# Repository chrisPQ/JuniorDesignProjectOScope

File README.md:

# JuniorDesignProjectOScope
Teensy program to run oscilloscope and output to screen

Video Overview: https://www.youtube.com/watch?v=Kpc6_z2Lm2U&ab_channel=MarshallG

Showcase Page: https://eecs.engineering.oregonstate.edu/project-showcase/projects/?id=eiNZnlOKVvULkvkf

Design Problem:
The design problem was to create a 2-channel oscilloscope. The scope needed to have voltage
scaling, time scaling, and trigger capabilities. The system also needs to have AC/DC coupling
modes, and a responsive interface.

Design process: The first step in our design process was to do some preliminary research to
see what it was we would need to accomplish the requirements. This included taking into
account the different choices of hardware we could use. We initially considered this project
based on a field programmable gate array due to the high sampling requirement that were
initially on the project instructions. After that requirement was removed, we went with our
second option, which was a Teensy 4.0 microcontroller board. We went with this option because
it is relatively inexpensive (especially compared to an FPGA), but it is still very fast with a clock
speed of 600 megahertz.

Our next big hurdle was figuring out how to implement the input circuitry. Since we decided our
input signal range was 0-20 volts peak to peak, and our microcontroller could only handle a
range of 0-3.3 volts, we had to adjust the signal to be able to measure it. We worked together on
designing the circuit and simulating the results in LTspice. We then soldered it to a protoboard
and experimented with the circuit in the lab. Our team had to work together to troubleshoot the
circuit and adjust the component values to perform as expected.

Although our whole system was split into individual blocks, we had to work together very closely
to ensure our systems would work as expected. For example, the input conditioning block has to
take voltage from the power supply block. Then the signal conversion and processing block had
to take input from the signal conditioning block.Communication about these individual tasks
made our system integration go smoother as the different pieces meshed together well.

Once all the circuit prototypes were designed and tested, we put them onto a PCB. We worked
together to peer review the PCB to ensure it would work correctly. Once the board arrived, we
used tools in the lab such as the oven and soldering irons to assemble the components onto the
board. This phase was a challenge as we included some very small surface mount parts in our
design. One challenge we had at this stage was that we had some slight mistakes in the PCB.
The pin header where the microcontroller was supposed to be ended up being one pin too
short. We fixed this by making an adapter board that mapped the pins of the MCU (expected
one two that we didn’t need) to a set of pin headers that was the correct number for the footprint
on the PCB.

We finished the process by working on our embedded software to control the device. This was a
challenge because it included meshing together code covering many different tasks, all of which
had challenges of their own.

Timeline:
April 19th: Engineering requirments devised.
April 26th: First block documentation.
May 1st: First Block verification.
May 10th: Second Block documentation
May 15th: Second block verification.
May 31st: System Verification.
June 5th: Demo of final project.

Takeaways:
Over the course of this project we learned about working on a complex project with a tight
deadline. This taught us many lessons of project management and how to focus on prioritizing
the important parts when it comes to developing electronics projects. Specifically we learned the
importance of researching and simulation methods before diving into them. While this may
seem restraining at first, it is a method that saves time and money in the long run because
things are more likely to work the first time around. We also learned many things about specific
technologies. Using direct memory access and interrupts to enhance the performance speed of
our microcontroller were concepts that required us to research and access data that wasn’t as
accessible as things we had worked on in the past.

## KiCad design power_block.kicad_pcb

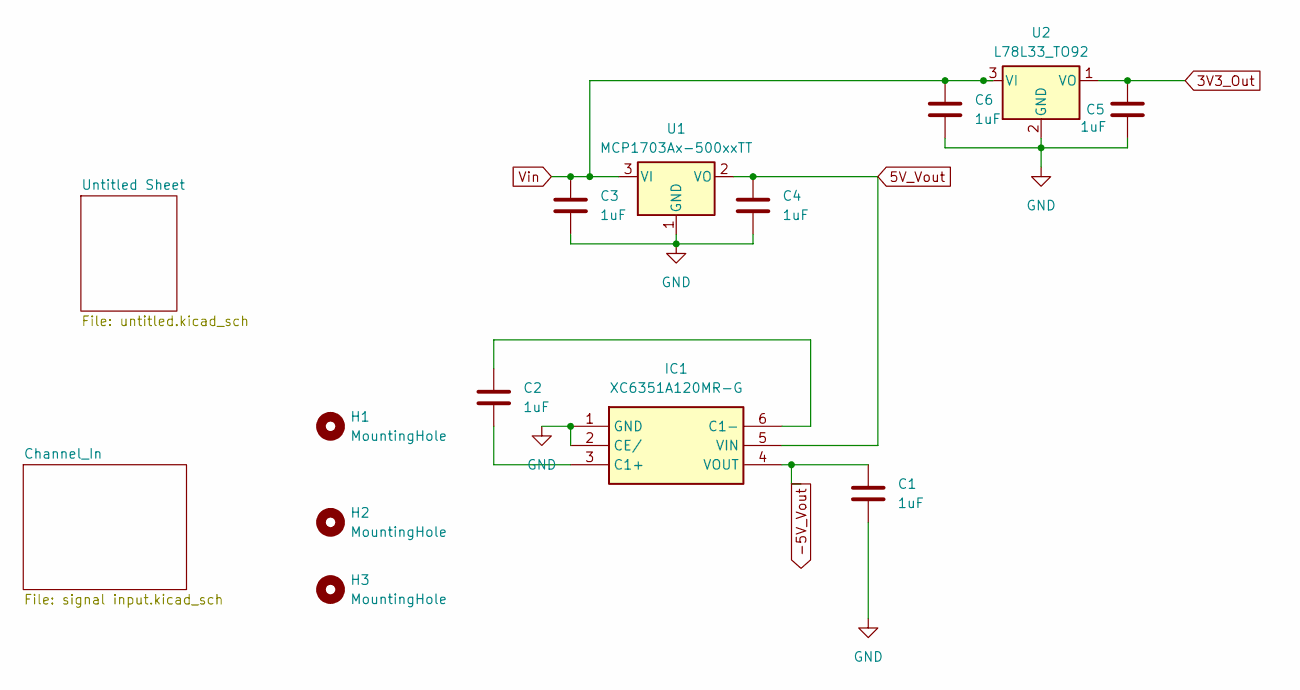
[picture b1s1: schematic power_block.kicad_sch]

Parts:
C1, C2, C3, C4, C5, C6: 1uF; C_0603_1608Metric_Pad1.08x0.95mm_HandSolder
H1, H2, H3: MountingHole; MountingHole_3.2mm_M3
IC1: XC6351A120MR-G; SOT-23-6; Mouser Part Number 865-XC6351A120MR-G
U1: MCP1703Ax-500xxTT; SOT-23
U2: L78L33_TO92; TO-92_Inline_Wide

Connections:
3V3_Out: C5.2, U2.1 (VO); also elsewhere on the board
5V_Vout: C4.1, IC1.5 (VIN), U1.2 (VO); also elsewhere on the board
-5V_Vout: C1.1, IC1.4 (VOUT); also elsewhere on the board
GND: C1.2, C3.2, C4.2, C5.1, C6.2, IC1.1 (GND), IC1.2 (CE/), U1.1 (GND), U2.2 (GND); also elsewhere on the board
unnamed: C2.2, IC1.3 (C1+)
unnamed: C2.1, IC1.6 (C1-)
Vin: C3.1, C6.1, U1.3 (VI), U2.3 (VI); also elsewhere on the board

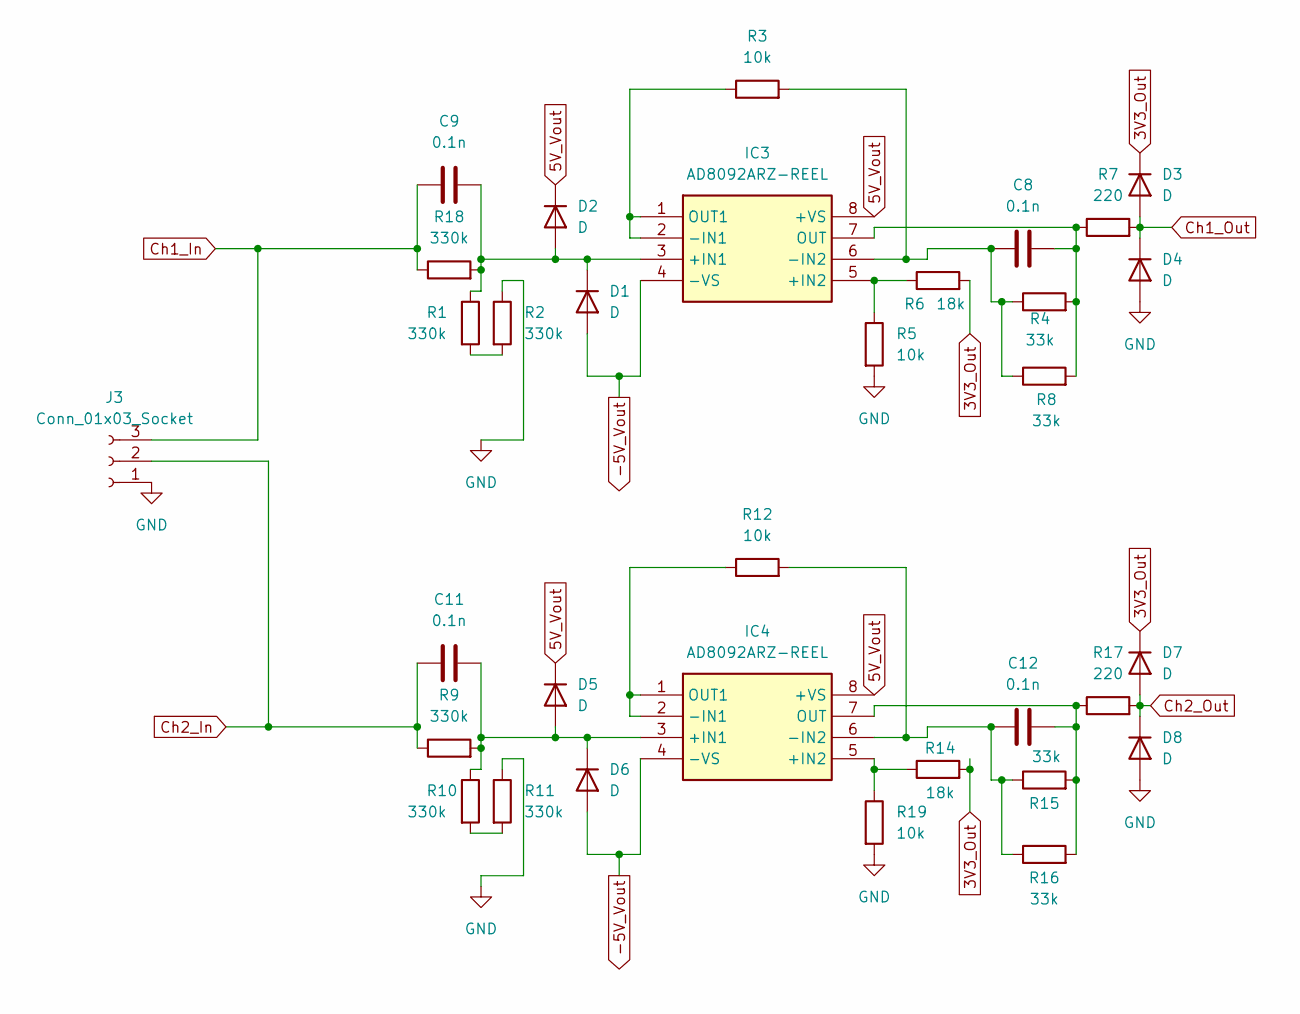
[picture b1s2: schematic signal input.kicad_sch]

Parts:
C8, C9, C11, C12: 0.1n; C_1206_3216Metric_Pad1.33x1.80mm_HandSolder
D1, D2, D3, D4, D5, D6, D7, D8: D; D_MiniMELF
IC3, IC4: AD8092ARZ-REEL; SOIC-8_3.9x4.9mm_P1.27mm; Mouser Part Number 584-AD8092ARZ-R
J3: Conn_01x03_Socket; JST_EH_B3B-EH-A_1x03_P2.50mm_Vertical
R1, R2, R9, R10, R11, R18: 330k; R_0805_2012Metric_Pad1.20x1.40mm_HandSolder
R3, R5, R12, R19: 10k; R_0805_2012Metric_Pad1.20x1.40mm_HandSolder
R4, R8, R15, R16: 33k; R_0603_1608Metric_Pad0.98x0.95mm_HandSolder
R6, R14: 18k; R_0603_1608Metric_Pad0.98x0.95mm_HandSolder
R7, R17: 220; R_1206_3216Metric_Pad1.30x1.75mm_HandSolder

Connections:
3V3_Out: D3.1 (K), D7.1 (K), R6.2, R14.2; also elsewhere on the board
5V_Vout: D2.1 (K), D5.1 (K), IC3.8 (+VS), IC4.8 (+VS); also elsewhere on the board
-5V_Vout: D1.2 (A), D6.2 (A), IC3.4 (-VS), IC4.4 (-VS); also elsewhere on the board
Ch1_In: C9.1, J3.3, R18.1
Ch1_Out: D3.2 (A), D4.1 (K), R7.2; also elsewhere on the board
Ch2_In: C11.1, J3.2, R9.1
Ch2_Out: D7.2 (A), D8.1 (K), R17.2; also elsewhere on the board
GND: D4.2 (A), D8.2 (A), J3.1, R2.1, R5.2, R11.1, R19.2; also elsewhere on the board
unnamed: C9.2, D1.1 (K), D2.2 (A), IC3.3 (+IN1), R1.1, R18.2
unnamed: C11.2, D5.2 (A), D6.1 (K), IC4.3 (+IN1), R9.2, R10.1
unnamed: IC3.5 (+IN2), R5.1, R6.1
unnamed: IC3.1 (OUT1), IC3.2 (-IN1), R3.1
unnamed: C8.1, IC3.6 (-IN2), R3.2, R4.1, R8.1
unnamed: C8.2, IC3.7 (OUT), R4.2, R7.1, R8.2
unnamed: IC4.5 (+IN2), R14.1, R19.1
unnamed: IC4.1 (OUT1), IC4.2 (-IN1), R12.1
unnamed: C12.1, IC4.6 (-IN2), R12.2, R15.1, R16.1
unnamed: C12.2, IC4.7 (OUT), R15.2, R16.2, R17.1
unnamed: R1.2, R2.2
unnamed: R10.2, R11.2

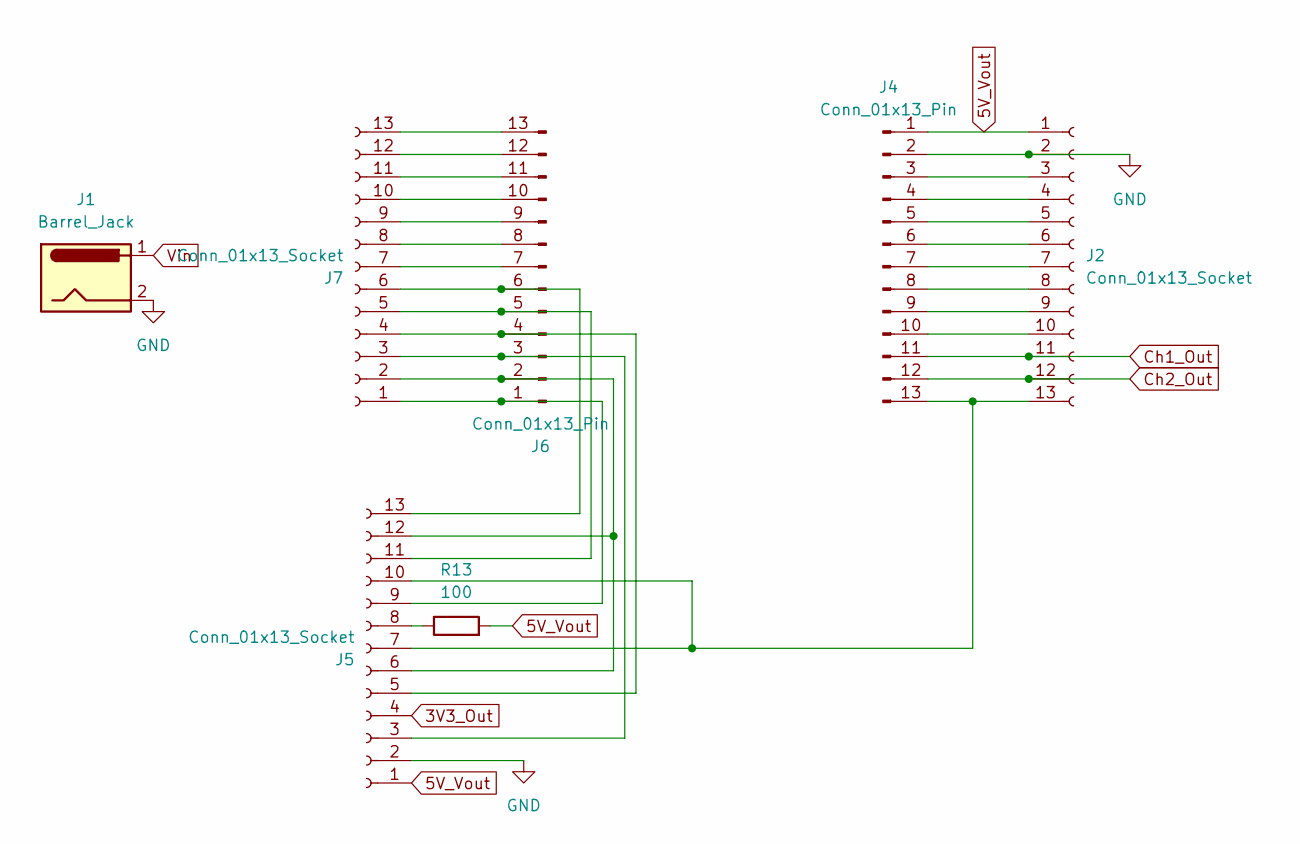
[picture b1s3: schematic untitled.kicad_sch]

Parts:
J1: Barrel_Jack; BarrelJack_GCT_DCJ200-10-A_Horizontal
J2, J5, J7: Conn_01x13_Socket; PinHeader_1x13_P2.54mm_Vertical
J4, J6: Conn_01x13_Pin; PinHeader_1x13_P2.54mm_Vertical
R13: 100; R_Axial_DIN0204_L3.6mm_D1.6mm_P7.62mm_Horizontal

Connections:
3V3_Out: J5.4; also elsewhere on the board
5V_Vout: J2.1, J4.1, J5.1, R13.2; also elsewhere on the board
Ch1_Out: J2.11, J4.11; also elsewhere on the board
Ch2_Out: J2.12, J4.12; also elsewhere on the board
GND: J1.2, J2.2, J4.2, J5.2; also elsewhere on the board
unnamed: J2.3, J4.3
unnamed: J2.4, J4.4
unnamed: J2.5, J4.5
unnamed: J2.6, J4.6
unnamed: J2.7, J4.7
unnamed: J2.8, J4.8
unnamed: J2.9, J4.9
unnamed: J2.10, J4.10
unnamed: J2.13, J4.13, J5.7, J5.10
unnamed: J5.3, J6.3, J7.3
unnamed: J5.5, J6.4, J7.4
unnamed: J5.8, R13.1
unnamed: J5.9, J6.1, J7.1
unnamed: J5.11, J6.5, J7.5
unnamed: J5.6, J5.12, J6.2, J7.2
unnamed: J5.13, J6.6, J7.6
unnamed: J6.7, J7.7
unnamed: J6.8, J7.8
unnamed: J6.9, J7.9
unnamed: J6.10, J7.10
unnamed: J6.11, J7.11
unnamed: J6.12, J7.12
unnamed: J6.13, J7.13
Vin: J1.1; also elsewhere on the board

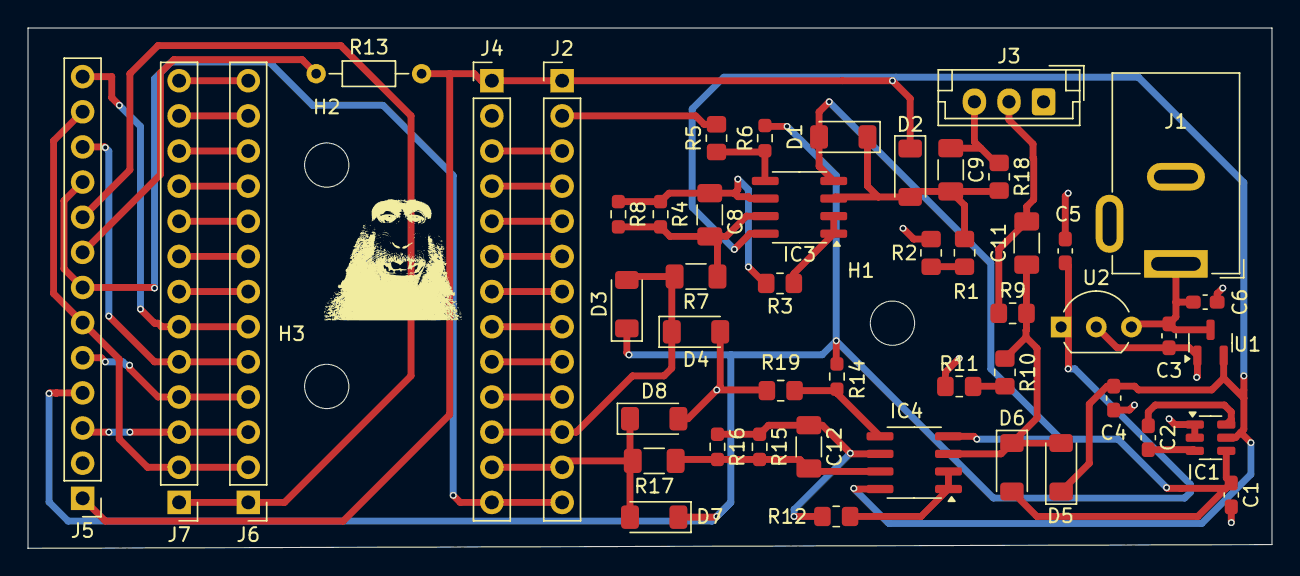
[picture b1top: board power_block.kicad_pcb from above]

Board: 2 copper layers, 89.9 x 37.6 mm, 52 parts (0 on the bottom side), 46 nets.

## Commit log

2024-05-15 Screen Testing Code for Arduino Mega
2024-05-31 KiCAD Files
2024-05-31 trigger_added
